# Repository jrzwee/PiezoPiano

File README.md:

# PiezoPiano
PiezoPiano is a PCB piano which can play one octave - all at once. It is programmed via Arduino. It is available for purchase in my [Tindie Store](https://www.tindie.com/products/zaan/piezo-piano/). 

If you like this project, feel free to support me 😇

## Setup for the Arduino IDE
This project is based on the great work of Hans with his [MegaCoreX](https://github.com/MCUdude/MegaCoreX). Visit this repo for further install instructions.
Select following settings in the Arduino IDE:

✅ **Board**: ATmega4809 \
✅ **COM Port**: Select the one your PiezoPiano is connected to \
✅ **Bootloader**: Optiboot (UART1 default pins) \
✅ **Pinout**: 48 pin standard

## Pinout

## Build of Material - BOM
TBD as there is a refactoring in the making.

## Renders

## License
[CERN-OHL-S](https://ohwr.org/cern_ohl_s_v2.pdf)

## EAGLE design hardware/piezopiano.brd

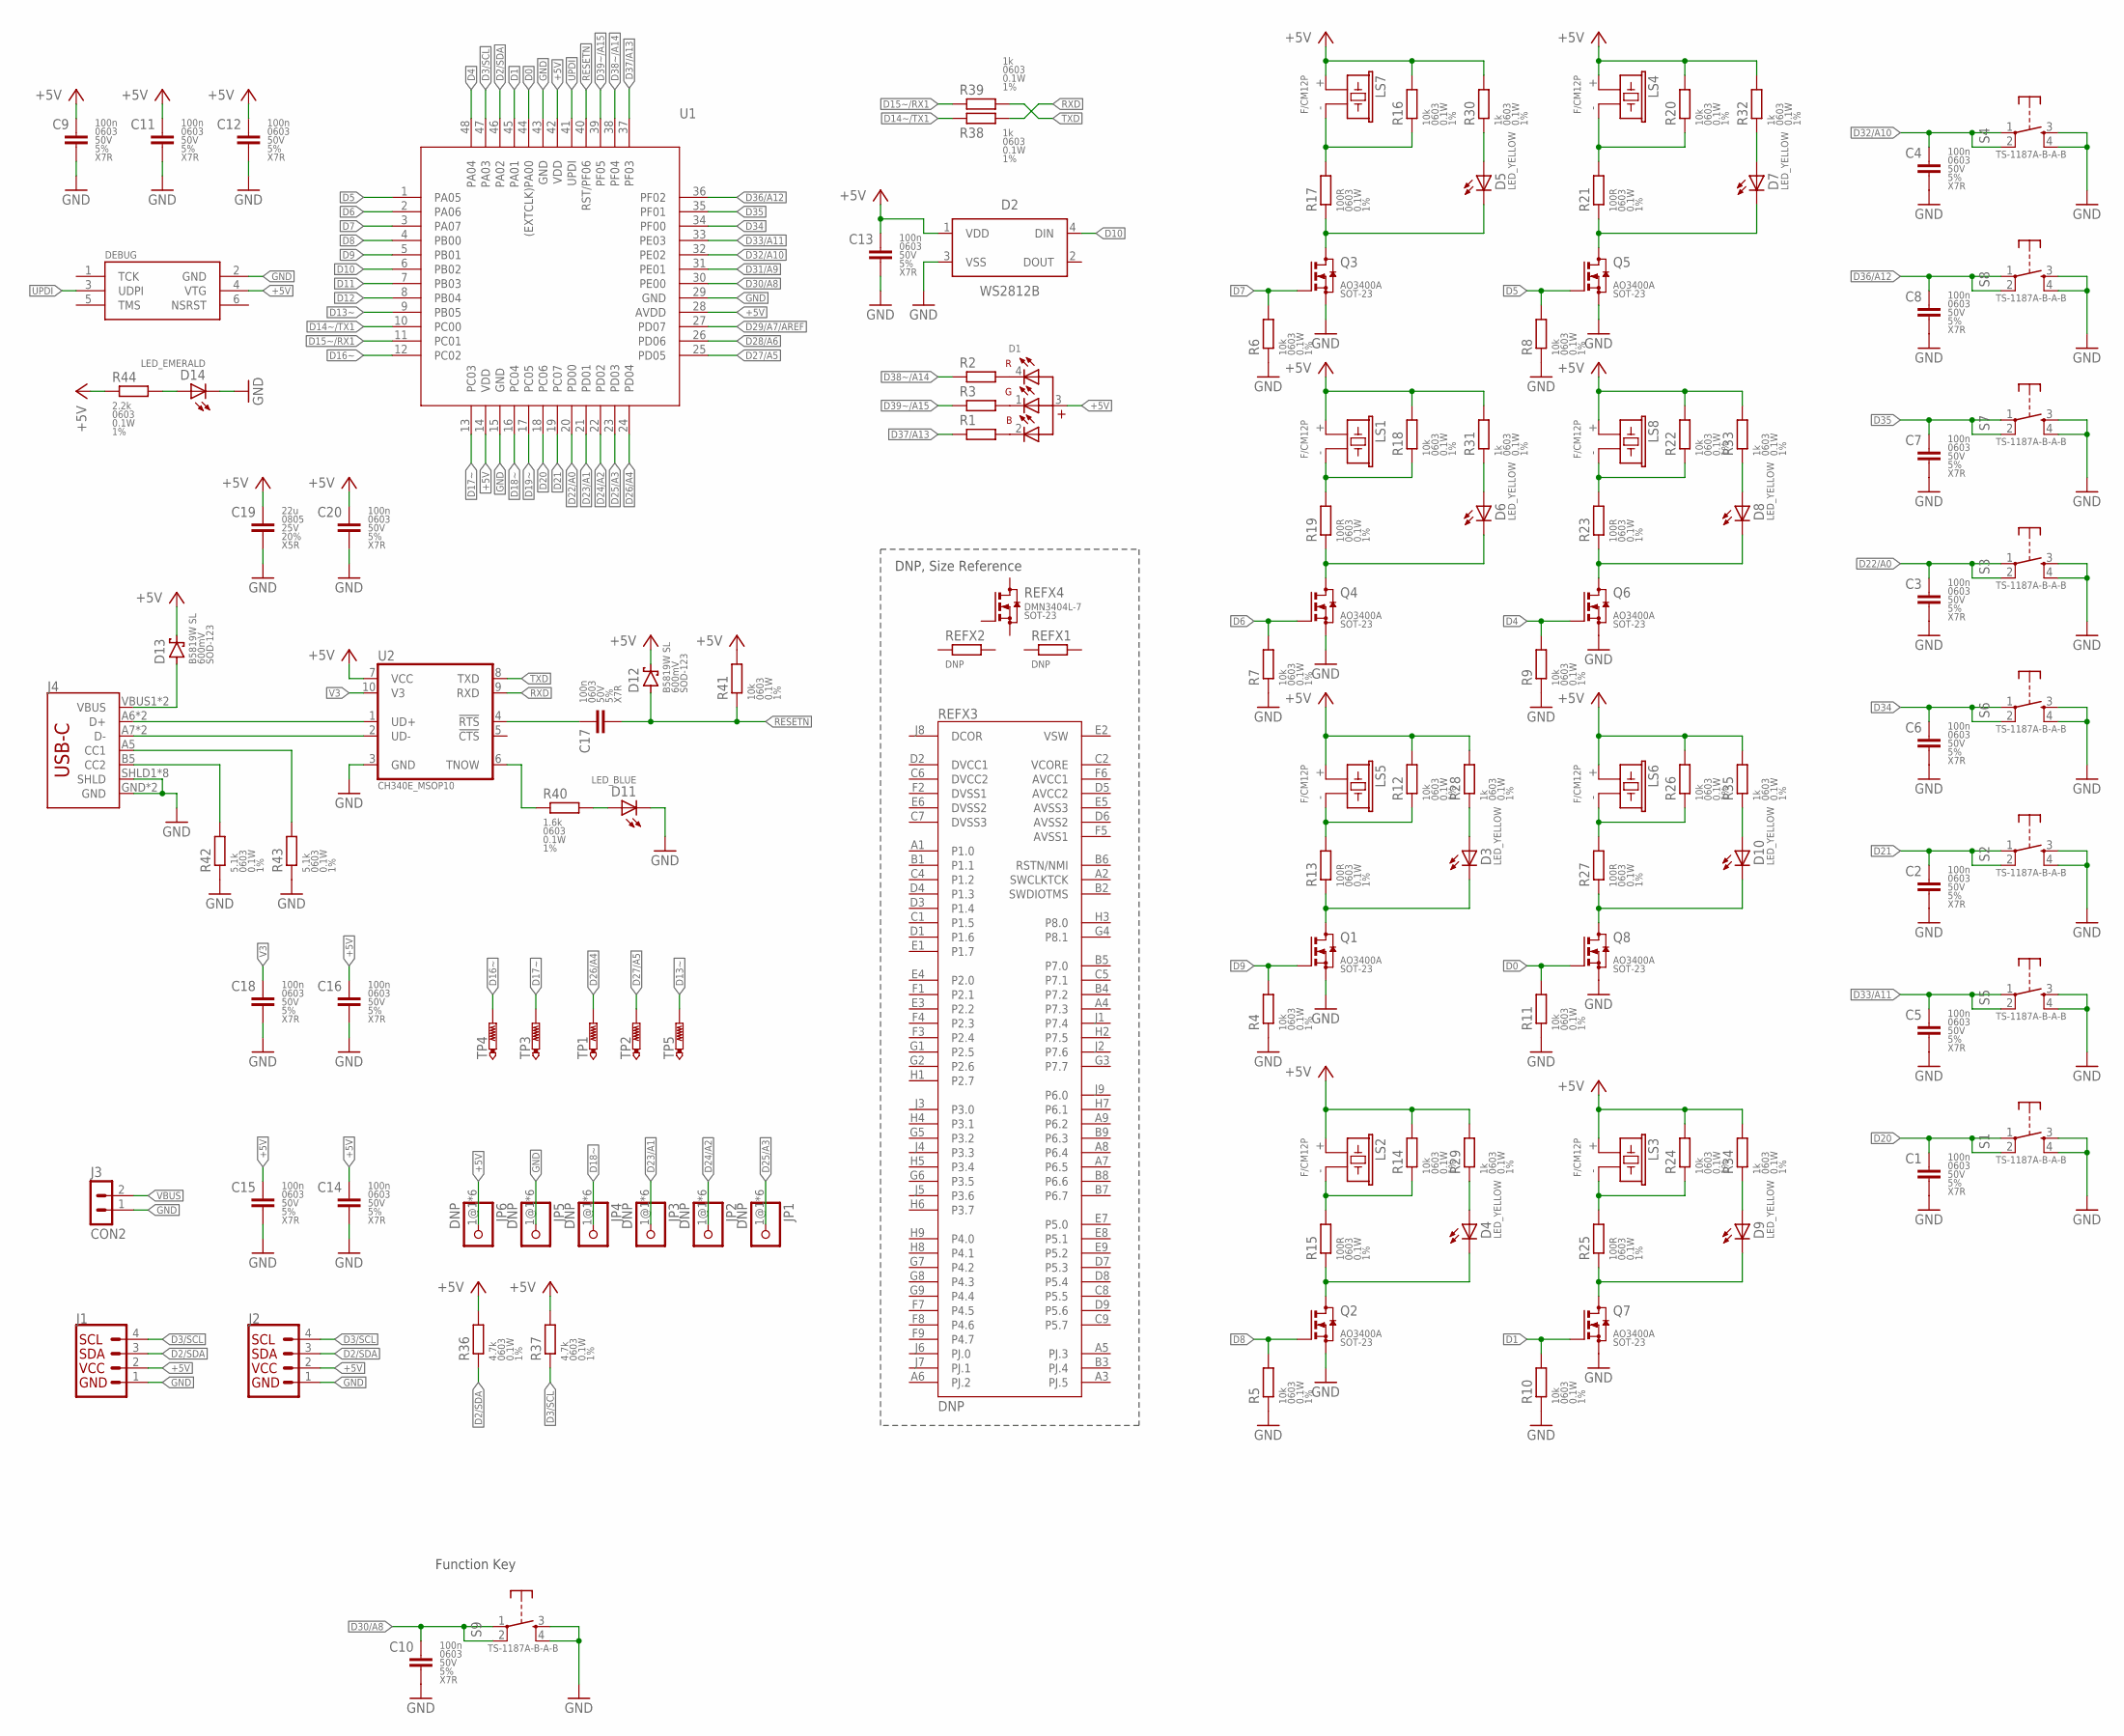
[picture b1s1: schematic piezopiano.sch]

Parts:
C1, C2, C3, C4, C5, C6, C7, C8, C9, C10, C11, C12, C13, C14, C15, C16, C17, C18, C20: 100n; C0603
C19: 22u; C0805
D1: E6C1209RGBC3UDAM173000; WL-SFCX_1210
D2: WS2812B
D3, D4, D5, D6, D7, D8, D9, D10: LED_YELLOW; LEDC1608X55N_FLAT
D11: LED_BLUE; LEDC1608X55N_FLAT
D12, D13: B5819WSL; SOD123
D14: LED_EMERALD; LEDC1608X55N_FLAT
DEBUG: DNP; 490107670612_DEBUGGING
J1, J2: QWIIC_CONNECTORJS-1MM; 1X04_1MM_RA
J3: CON2; H2-2.54
J4: USB_C2-LAYER; USB-C-16P
JP1, JP2, JP3, JP4, JP5, JP6: DNP; 1X01
LS1, LS2, LS3, LS4, LS5, LS6, LS7, LS8: F/CM12P; CM12P/5.0P
Q1, Q2, Q3, Q4, Q5, Q6, Q7, Q8: AO3400A; SOT23
R1, R40: 1.6k; R0603
R2, R28, R29, R30, R31, R32, R33, R34, R35, R38, R39: 1k; R0603
R3, R44: 2.2k; R0603
R4, R5, R6, R7, R8, R9, R10, R11, R12, R14, R16, R18, R20, R22, R24, R26, R41: 10k; R0603
R13, R15, R17, R19, R21, R23, R25, R27: 100R; R0603
R36, R37: 4.7k; R0603
R42, R43: 5.1k; R0603
REFX1: DNP; R0603
REFX2: DNP; R0805
REFX3: DNP; BGA80
REFX4: DNP; SOT23
S1, S2, S3, S4, S5, S6, S7, S8, S9: TS-1187A-B-A-B; TACTILE_SWITCH_SMD_5.2MM
TP1, TP2, TP3, TP4, TP5: PTR1B1,27; B1,27
U1: ATMEGA4809; TQFP48
U2: CH340E_MSOP10; MSOP10

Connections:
+5V: C9.1, C11.1, C12.1, C13.1, C14.1, C15.1, C16.1, C19.1, C20.1, D1.3 (4), D2.1 (VDD), D12.C, D13.C, DEBUG.4 (VTG), J1.2 (VCC), J2.2 (VCC), JP6.1@1, JP6.1@2, JP6.1@3, JP6.1@4, JP6.1@5, JP6.1@6, LS1.+ (1), LS2.+ (1), LS3.+ (1), LS4.+ (1), LS5.+ (1), LS6.+ (1), LS7.+ (1), LS8.+ (1), R12.2, R14.2, R16.2, R18.2, R20.2, R22.2, R24.2, R26.2, R28.2, R29.2, R30.2, R31.2, R32.2, R33.2, R34.2, R35.2, R36.2, R37.2, R41.2, R44.1, U1.14 (VDD), U1.28 (AVDD), U1.42 (VDD), U2.7 (VCC)
AVCC1: REFX3.F6 (AVCC1)
AVCC2: REFX3.D5 (AVCC2)
AVSS1: REFX3.F5 (AVSS1)
AVSS2: REFX3.D6 (AVSS2)
AVSS3: REFX3.E5 (AVSS3)
D0: Q8.1 (G), R11.2, U1.44 ((EXTCLK)PA00)
D1: Q7.1 (G), R10.2, U1.45 (PA01)
D2/SDA: J1.3 (SDA), J2.3 (SDA), R36.1, U1.46 (PA02)
D3/SCL: J1.4 (SCL), J2.4 (SCL), R37.1, U1.47 (PA03)
D4: Q6.1 (G), R9.2, U1.48 (PA04)
D5: Q5.1 (G), R8.2, U1.1 (PA05)
D6: Q4.1 (G), R7.2, U1.2 (PA06)
D7: Q3.1 (G), R6.2, U1.3 (PA07)
D8: Q2.1 (G), R5.2, U1.4 (PB00)
D9: Q1.1 (G), R4.2, U1.5 (PB01)
D10: D2.4 (DIN), U1.6 (PB02)
D11: U1.7 (PB03)
D12: U1.8 (PB04)
D13~: TP5.TP, U1.9 (PB05)
D14~/TX1: R38.1, U1.10 (PC00)
D15~/RX1: R39.1, U1.11 (PC01)
D16~: TP4.TP, U1.12 (PC02)
D17~: TP3.TP, U1.13 (PC03)
D18~: JP4.1@1, JP4.1@2, JP4.1@3, JP4.1@4, JP4.1@5, JP4.1@6, U1.16 (PC04)
D19~: U1.17 (PC05)
D20: C1.1, S1.1, S1.2, U1.18 (PC06)
D21: C2.1, S2.1, S2.2, U1.19 (PC07)
D22/A0: C3.1, S3.1, S3.2, U1.20 (PD00)
D23/A1: JP3.1@1, JP3.1@2, JP3.1@3, JP3.1@4, JP3.1@5, JP3.1@6, U1.21 (PD01)
D24/A2: JP2.1@1, JP2.1@2, JP2.1@3, JP2.1@4, JP2.1@5, JP2.1@6, U1.22 (PD02)
D25/A3: JP1.1@1, JP1.1@2, JP1.1@3, JP1.1@4, JP1.1@5, JP1.1@6, U1.23 (PD03)
D26/A4: TP1.TP, U1.24 (PD04)
D27/A5: TP2.TP, U1.25 (PD05)
D28/A6: U1.26 (PD06)
D29/A7/AREF: U1.27 (PD07)
D30/A8: C10.1, S9.1, S9.2, U1.30 (PE00)
D31/A9: U1.31 (PE01)
D32/A10: C4.1, S4.1, S4.2, U1.32 (PE02)
D33/A11: C5.1, S5.1, S5.2, U1.33 (PE03)
D34: C6.1, S6.1, S6.2, U1.34 (PF00)
D35: C7.1, S7.1, S7.2, U1.35 (PF01)
D36/A12: C8.1, S8.1, S8.2, U1.36 (PF02)
D37/A13: R1.1, U1.37 (PF03)
D38~/A14: R2.1, U1.38 (PF04)
D39~/A15: R3.1, U1.39 (PF05)
DCOR: REFX3.J8 (DCOR)
DVCC1: REFX3.D2 (DVCC1)
DVCC2: REFX3.C6 (DVCC2)
DVSS1: REFX3.F2 (DVSS1)
DVSS2: REFX3.E6 (DVSS2)
DVSS3: REFX3.C7 (DVSS3)
GND: C1.2, C2.2, C3.2, C4.2, C5.2, C6.2, C7.2, C8.2, C9.2, C10.2, C11.2, C12.2, C13.2, C14.2, C15.2, C16.2, C18.2, C19.2, C20.2, D2.3 (VSS), D11.C, D14.C, DEBUG.2 (GND), J1.1 (GND), J2.1 (GND), J3.1, J4.GND, J4.GND2 (GND), J4.SHLD1 (SHLD), J4.SHLD2 (SHLD), J4.SHLD3 (SHLD), J4.SHLD4 (SHLD), J4.SHLD5 (SHLD), J4.SHLD6 (SHLD), J4.SHLD7 (SHLD), J4.SHLD8 (SHLD), JP5.1@1, JP5.1@2, JP5.1@3, JP5.1@4, JP5.1@5, JP5.1@6, Q1.2 (S), Q2.2 (S), Q3.2 (S), Q4.2 (S), Q5.2 (S), Q6.2 (S), Q7.2 (S), Q8.2 (S), R4.1, R5.1, R6.1, R7.1, R8.1, R9.1, R10.1, R11.1, R42.1, R43.1, S1.3 (S), S1.4 (S), S2.3 (S), S2.4 (S), S3.3 (S), S3.4 (S), S4.3 (S), S4.4 (S), S5.3 (S), S5.4 (S), S6.3 (S), S6.4 (S), S7.3 (S), S7.4 (S), S8.3 (S), S8.4 (S), S9.3 (S), S9.4 (S), U1.15 (GND), U1.29 (GND), U1.43 (GND), U2.3 (GND)
unnamed: C17.1, U2.4 (!RTS)
unnamed: D6.C, Q4.3 (D), R19.1
unnamed: D3.C, Q1.3 (D), R13.1
unnamed: LS2.- (2), R14.1, R15.2
unnamed: D7.C, Q5.3 (D), R21.1
unnamed: LS8.- (2), R22.1, R23.2
unnamed: D10.C, Q8.3 (D), R27.1
unnamed: D14.A, R44.2
unnamed: D5.C, Q3.3 (D), R17.1
unnamed: LS1.- (2), R18.1, R19.2
unnamed: LS5.- (2), R12.1, R13.2
unnamed: D4.C, Q2.3 (D), R15.1
unnamed: LS4.- (2), R20.1, R21.2
unnamed: D8.C, Q6.3 (D), R23.1
unnamed: LS6.- (2), R26.1, R27.2
unnamed: LS3.- (2), R24.1, R25.2
unnamed: D9.C, Q7.3 (D), R25.1
unnamed: LS7.- (2), R16.1, R17.2
unnamed: R40.1, U2.6 (TNOW)
unnamed: D11.A, R40.2
unnamed: D1.4 (R), R2.2
unnamed: D5.A, R30.1
unnamed: D7.A, R32.1
unnamed: D8.A, R33.1
unnamed: D6.A, R31.1
unnamed: D10.A, R35.1
unnamed: D3.A, R28.1
unnamed: D1.2 (B), R1.2
unnamed: J4.B5 (CC2), R42.2
unnamed: J4.A5 (CC1), R43.2
unnamed: J4.A6 (D+), J4.B6 (D+), U2.1 (UD+)
unnamed: J4.A7 (D-), J4.B7 (D-), U2.2 (UD-)
unnamed: D4.A, R29.1
unnamed: D9.A, R34.1
unnamed: D1.1 (G), R3.2
RESETN: C17.2, D12.A, R41.1, U1.40 (RST/PF06)
RXD: R38.2, U2.9 (RXD)
TXD: R39.2, U2.8 (TXD)
UPDI: DEBUG.3 (UDPI), U1.41 (UPDI)
V3: C18.1, U2.10 (V3)
VBUS: D13.A, J3.2, J4.VBUS1 (VBUS), J4.VBUS2 (VBUS)
VCORE: REFX3.C2 (VCORE)
VSW: REFX3.E2 (VSW)

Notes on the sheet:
DNP, Size Reference
Function Key

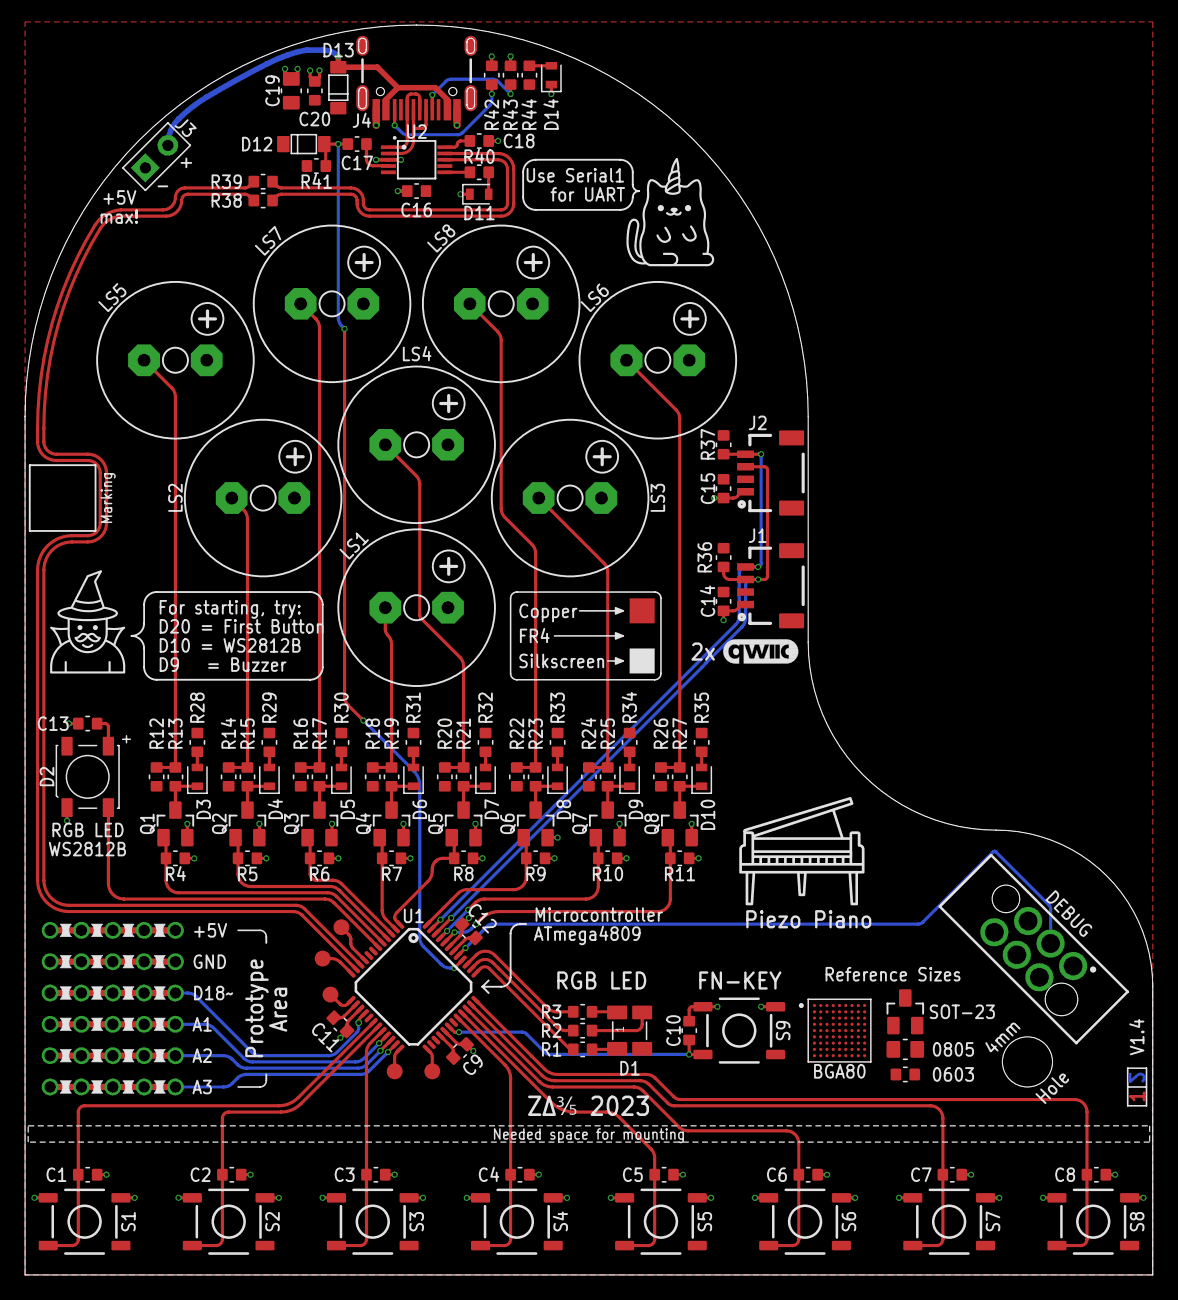
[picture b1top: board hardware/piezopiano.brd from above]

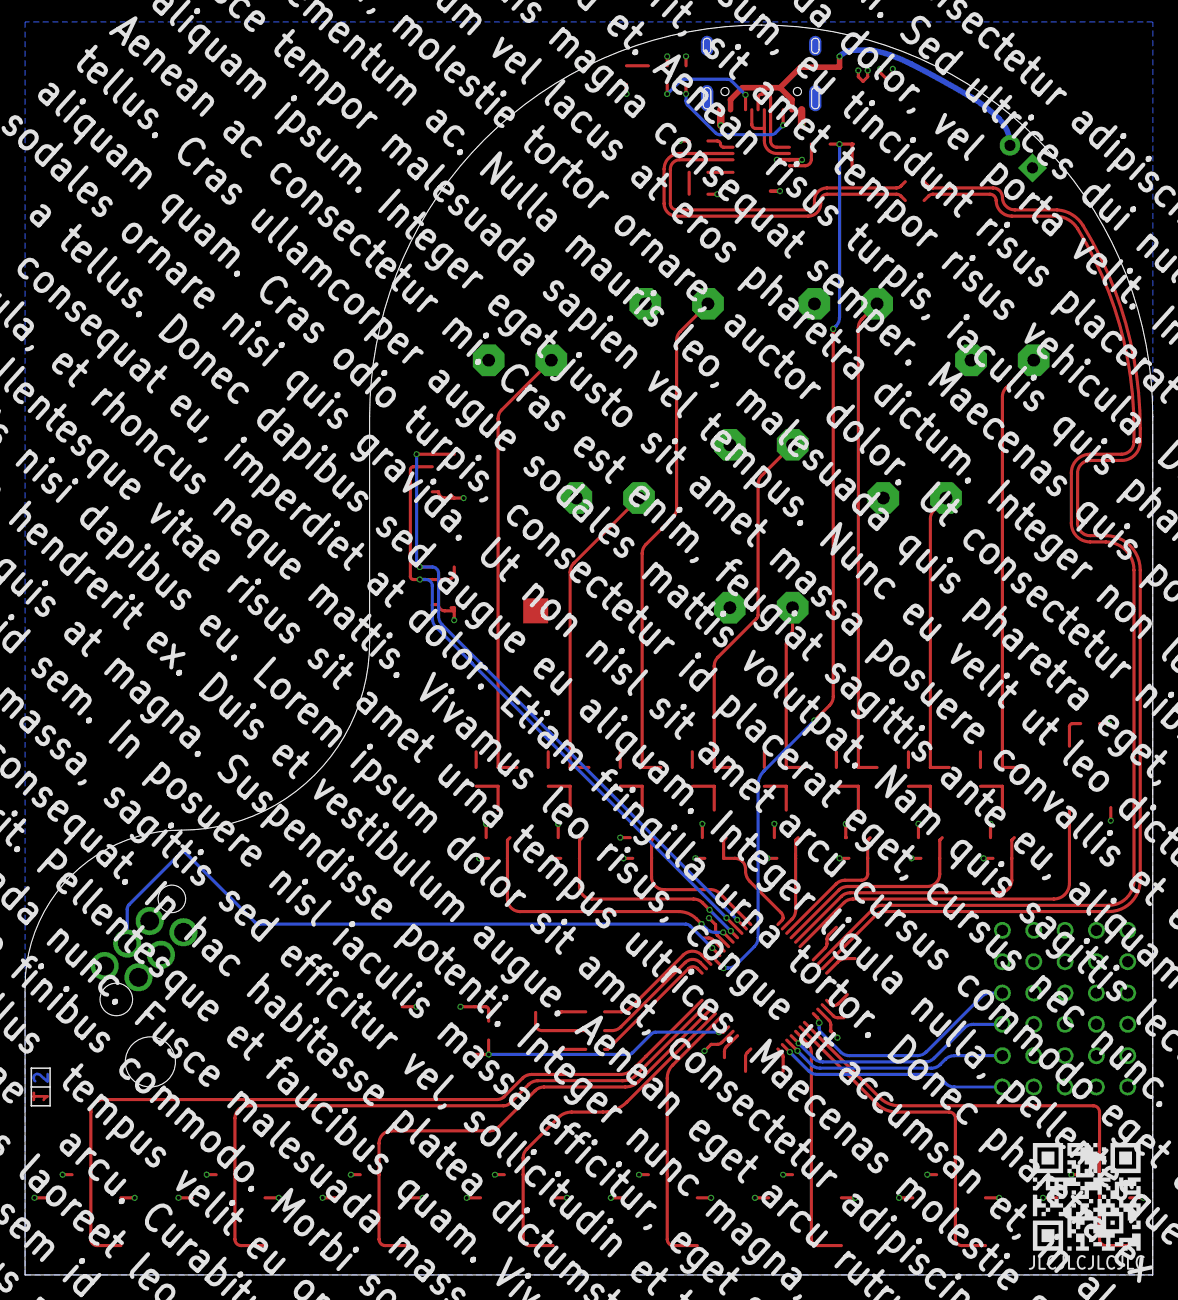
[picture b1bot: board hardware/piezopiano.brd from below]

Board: 2 copper layers, 90.0 x 99.7 mm, 134 parts (2 on the bottom side), 77 nets.

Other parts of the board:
U$1: STACKUP-2L
U$2: PIANO-10MM
U$3: WIZARD-6MM
U$4: QWIIC_6MM
U$5: EXPLANATION-2-2MM
U$6: QR-SPACE
U$7: CATICORN-7MM
U$100: GITHUB-JRZ-10
U$101: JLC_UID

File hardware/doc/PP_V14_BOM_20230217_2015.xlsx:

Model | PP
Version | V1.4
BOM Revision | A
Initials | AZ
Date | 2023-02-17
Description | Qty | Parts | Value | MPN | MF | Info
Chip Capacitor | 19 | C1, C2, C3, C4, C5, C6, C7, C8, C9, C10, C11, C12, C13, C14, C15, C16, C17, C18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 | 100n 0603 50V X7R 5% | CC0603JRX7R9BB104 | Yageo
Chip Resistor | 17 | R4, R5, R6, R7, R8, R9, R10, R11, R12, R14, R16, R18, R20, R22, R24, R26, R41 | 10k 0603 75V 1% | RC0603FR-0710KL | Yageo
Chip Resistor | 11 | R2, R28, R29, R30, R31, R32, R33, R34, R35, R38, R39 | 1k 0603 75V 1% | RC0603FR-071KL | Yageo
Tactile Button SMD | 9 | S1, S2, S3, S4, S5, S6, S7, S8, S9 |  | TS-1187A-B-A-B | XKB Connectivity
Chip Resistor | 8 | R13, R15, R17, R19, R21, R23, R25, R27 | 100R 0603 75V 1% | RC0603FR-07100RL | Yageo
N-CHANNEL MOSFET | 8 | Q1, Q2, Q3, Q4, Q5, Q6, Q7, Q8 | SOT-23 | AO3400A | Alpha & Omega Semicon
Piezo Buzzer | 8 | LS1, LS2, LS3, LS4, LS5, LS6, LS7, LS8 |  | ZL-YDW1207-4005PA-5.0 | ZLFY
CHIP LED FLAT | 8 | D3, D4, D5, D6, D7, D8, D9, D10 | LED_YELLOW | 19-213/Y2C-CQ2R2L/3T(CY) | Everlight Elec
Header SMD 1MM 4Pin | 2 | J1, J2 |  | C145956 | BOOMELE
Chip Resistor | 2 | R1, R40 | 1.6k 0603 75V 1% | RC0603FR-071K6L | Yageo
Chip Resistor | 2 | R36, R37 | 4.7k 0603 75V 1% | RC0603FR-074K7L | Yageo
Chip Resistor | 2 | R42, R43 | 5.1k 0603 75V 1% | RC0603FR-075K1L | Yageo
Schottky Diode | 2 | D12, D13 | SOD-123 | B5819W SL | Changjiang Electronics Tech (CJ)
RGB SMD LED | 1 | D1 | 1210 | E6C1209RGBC3UDA | EKINGLUX
USB Type C Female | 1 | J4 | USB-C 16P | YTC-TC16S-23 | YIYUAN
Chip Resistor | 1 | R3, R44 | 2.2k 0603 75V 1% | RC0603FR-072K2L | Yageo
Chip Capacitor | 1 | C19 | 22u 0805 25V X5R 20% | GRM21BR61E226ME44L | Murata
ATmega4809 Microcontroller | 1 | U1 |  | ATMEGA4809-AFR | Microchip
UART Converter | 1 | U2 | MSOP-10 | CH340E | Jiangsu Qin Heng
CHIP LED FLAT | 1 | D11 | LED_BLUE | 19-217/GHC-YR1S2/3T | Everlight Elec
CHIP LED FLAT | 1 | D14 | LED_EMERALD | 19-217/BHC-ZL1M2RY/3T | Everlight Elec
WS2812 RGB LED | 1 | D2 |  | WS2812B-B/W | WORLDSEMI

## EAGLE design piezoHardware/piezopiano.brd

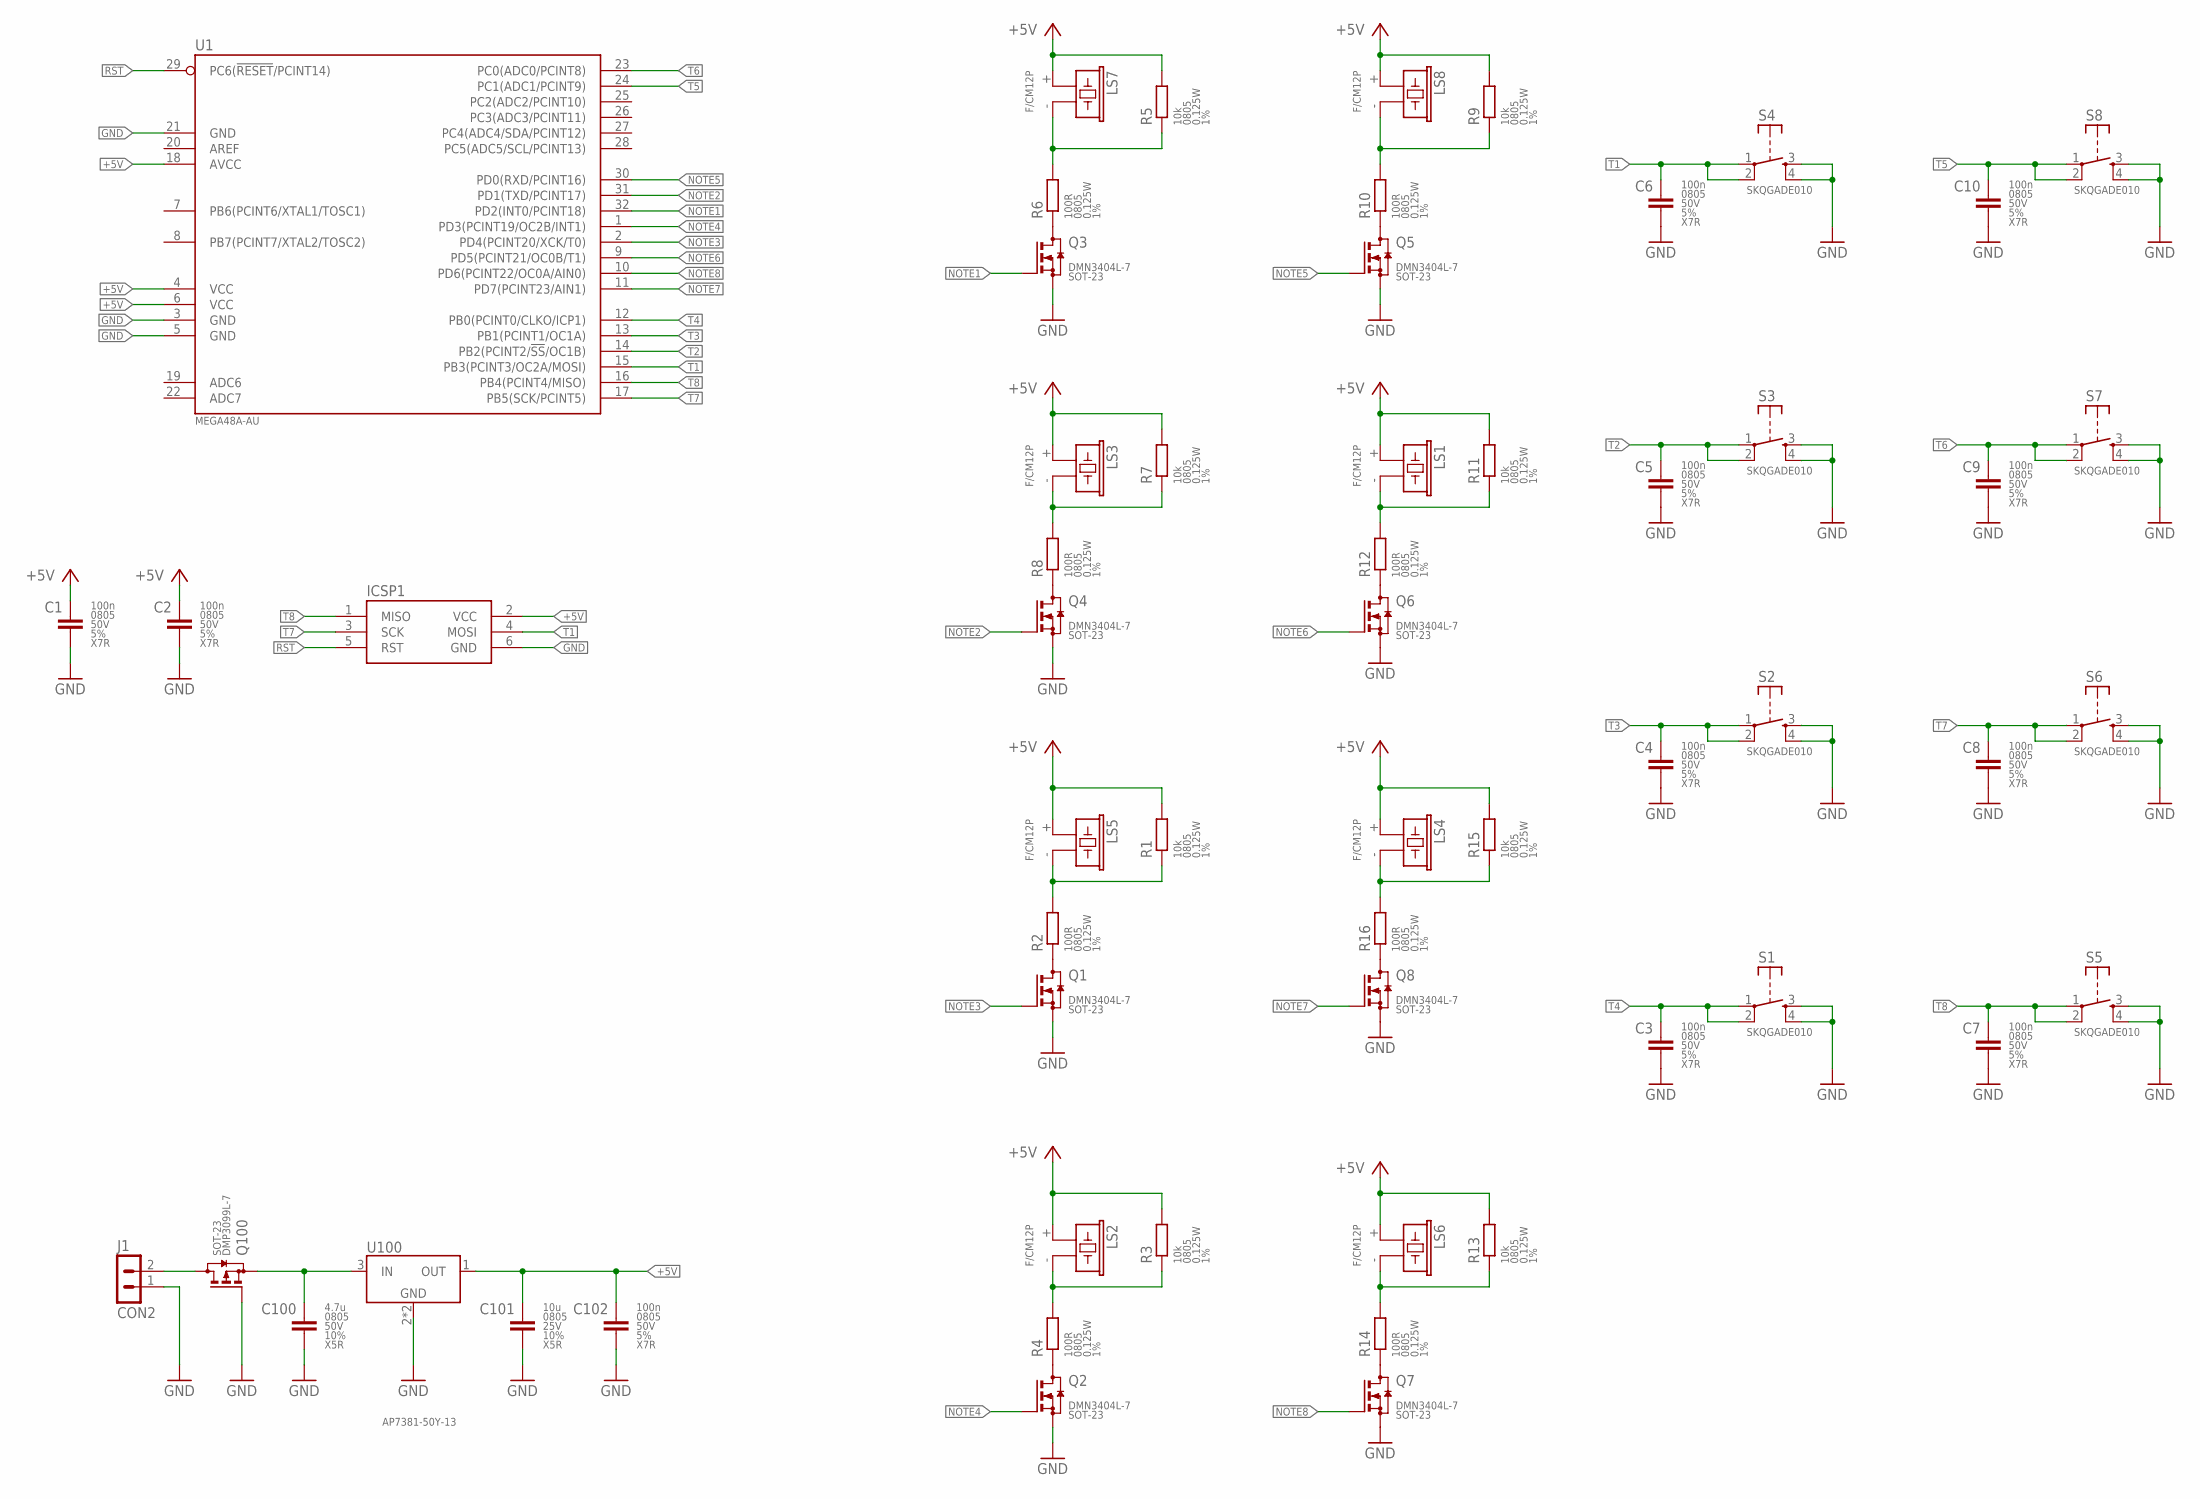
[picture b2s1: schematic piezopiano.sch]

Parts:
C1, C2, C3, C4, C5, C6, C7, C8, C9, C10, C102: 100n; C0805
C100: 4.7u; C0805
C101: 10u; C0805
ICSP1: AVRISP2.54MM; AVRISP-2.54
J1: CON2; H2-2.54
LS1, LS2, LS3, LS4, LS5, LS6, LS7, LS8: F/CM12P; CM12P/5.0P
Q1, Q2, Q3, Q4, Q5, Q6, Q7, Q8: DMN3404L; SOT23
Q100: DMP3099L; SOT23
R1, R3, R5, R7, R9, R11, R13, R15: 10k; R0805
R2, R4, R6, R8, R10, R12, R14, R16: 100R; R0805
S1, S2, S3, S4, S5, S6, S7, S8: SKQGADE010; TACTILE_SWITCH_SMD_5.2MM
U1: MEGA48A-AU; TQFP32-08
U100: AP7381-50Y-13; SOT89

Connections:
+5V: C1.1, C2.1, C101.1, C102.1, ICSP1.2 (VCC), LS1.+ (1), LS2.+ (1), LS3.+ (1), LS4.+ (1), LS5.+ (1), LS6.+ (1), LS7.+ (1), LS8.+ (1), R1.2, R3.2, R5.2, R7.2, R9.2, R11.2, R13.2, R15.2, U1.4 (VCC), U1.6 (VCC), U1.18 (AVCC), U100.1 (OUT)
GND: C1.2, C2.2, C3.2, C4.2, C5.2, C6.2, C7.2, C8.2, C9.2, C10.2, C100.2, C101.2, C102.2, ICSP1.6 (GND), J1.1, Q1.2 (S), Q2.2 (S), Q3.2 (S), Q4.2 (S), Q5.2 (S), Q6.2 (S), Q7.2 (S), Q8.2 (S), Q100.1 (G), S1.3 (S), S1.4 (S), S2.3 (S), S2.4 (S), S3.3 (S), S3.4 (S), S4.3 (S), S4.4 (S), S5.3 (S), S5.4 (S), S6.3 (S), S6.4 (S), S7.3 (S), S7.4 (S), S8.3 (S), S8.4 (S), U1.3 (GND), U1.5 (GND), U1.21 (GND), U100.2 (GND), U100.2@1 (GND)
unnamed: J1.2, Q100.3 (D)
unnamed: Q4.3 (D), R8.1
unnamed: Q1.3 (D), R2.1
unnamed: LS2.- (2), R3.1, R4.2
unnamed: Q5.3 (D), R10.1
unnamed: LS1.- (2), R11.1, R12.2
unnamed: Q8.3 (D), R16.1
unnamed: Q7.3 (D), R14.1
unnamed: Q3.3 (D), R6.1
unnamed: LS3.- (2), R7.1, R8.2
unnamed: LS5.- (2), R1.1, R2.2
unnamed: Q2.3 (D), R4.1
unnamed: LS8.- (2), R9.1, R10.2
unnamed: Q6.3 (D), R12.1
unnamed: LS4.- (2), R15.1, R16.2
unnamed: LS6.- (2), R13.1, R14.2
unnamed: C100.1, Q100.2 (S), U100.3 (IN)
unnamed: LS7.- (2), R5.1, R6.2
NOTE1: Q3.1 (G), U1.32 (PD2(INT0/PCINT18))
NOTE2: Q4.1 (G), U1.31 (PD1(TXD/PCINT17))
NOTE3: Q1.1 (G), U1.2 (PD4(PCINT20/XCK/T0))
NOTE4: Q2.1 (G), U1.1 (PD3(PCINT19/OC2B/INT1))
NOTE5: Q5.1 (G), U1.30 (PD0(RXD/PCINT16))
NOTE6: Q6.1 (G), U1.9 (PD5(PCINT21/OC0B/T1))
NOTE7: Q8.1 (G), U1.11 (PD7(PCINT23/AIN1))
NOTE8: Q7.1 (G), U1.10 (PD6(PCINT22/OC0A/AIN0))
RST: ICSP1.5 (RST), U1.29 (PC6(!RESET!/PCINT14))
T1: C6.1, ICSP1.4 (MOSI), S4.1, S4.2, U1.15 (PB3(PCINT3/OC2A/MOSI))
T2: C5.1, S3.1, S3.2, U1.14 (PB2(PCINT2/!SS!/OC1B))
T3: C4.1, S2.1, S2.2, U1.13 (PB1(PCINT1/OC1A))
T4: C3.1, S1.1, S1.2, U1.12 (PB0(PCINT0/CLKO/ICP1))
T5: C10.1, S8.1, S8.2, U1.24 (PC1(ADC1/PCINT9))
T6: C9.1, S7.1, S7.2, U1.23 (PC0(ADC0/PCINT8))
T7: C8.1, ICSP1.3 (SCK), S6.1, S6.2, U1.17 (PB5(SCK/PCINT5))
T8: C7.1, ICSP1.1 (MISO), S5.1, S5.2, U1.16 (PB4(PCINT4/MISO))

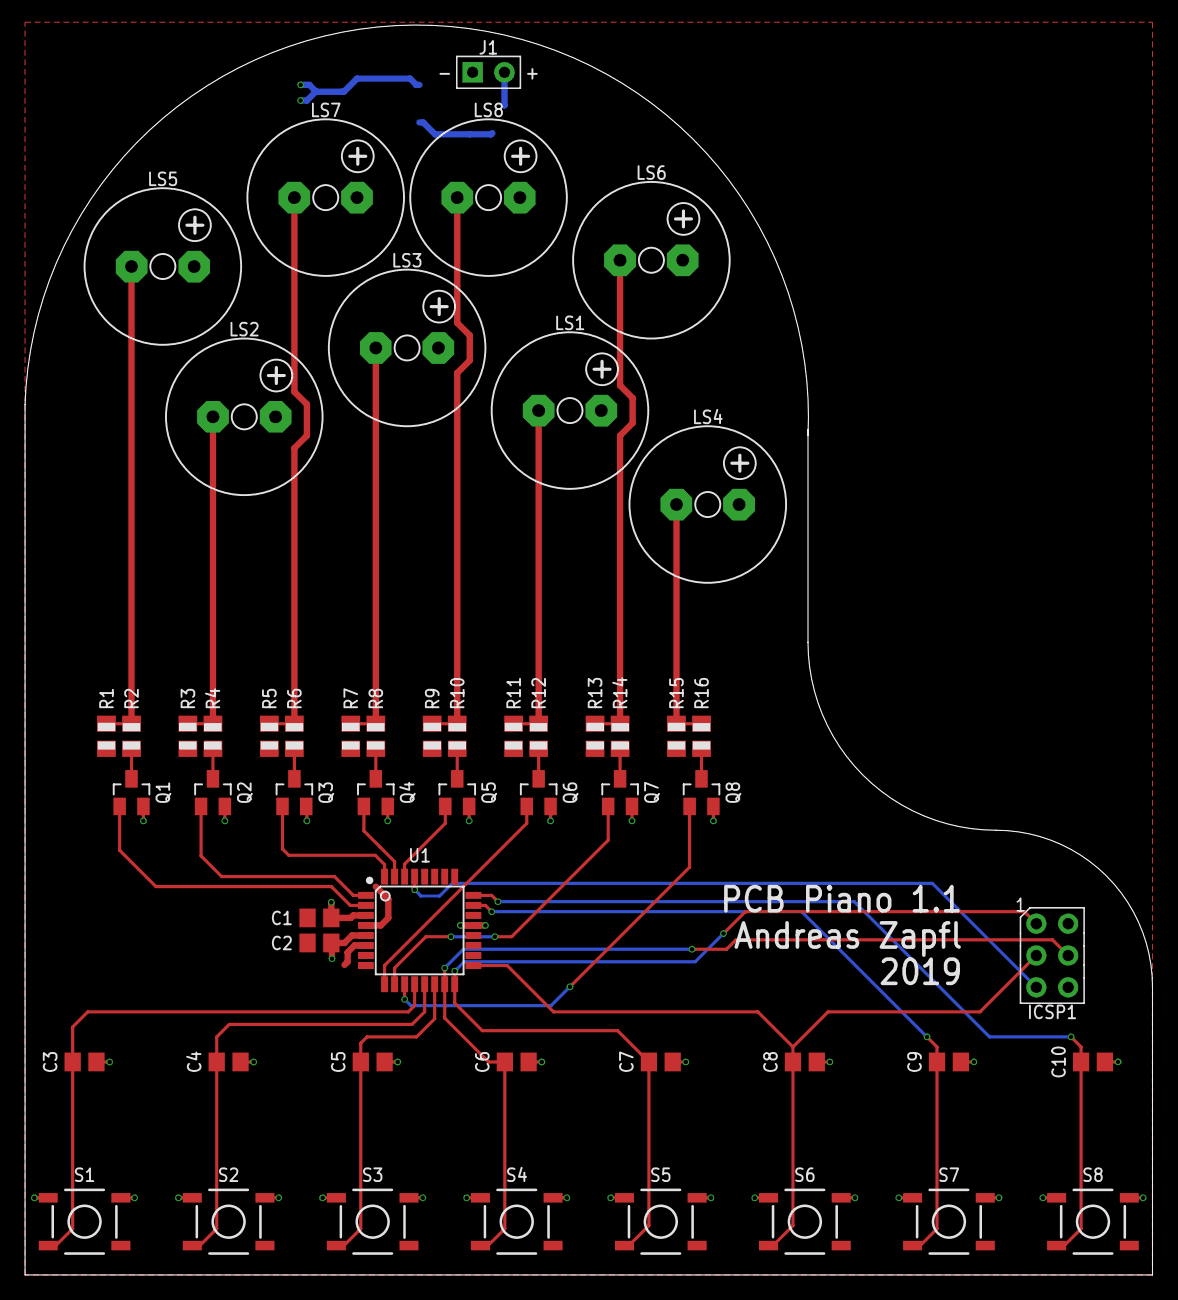
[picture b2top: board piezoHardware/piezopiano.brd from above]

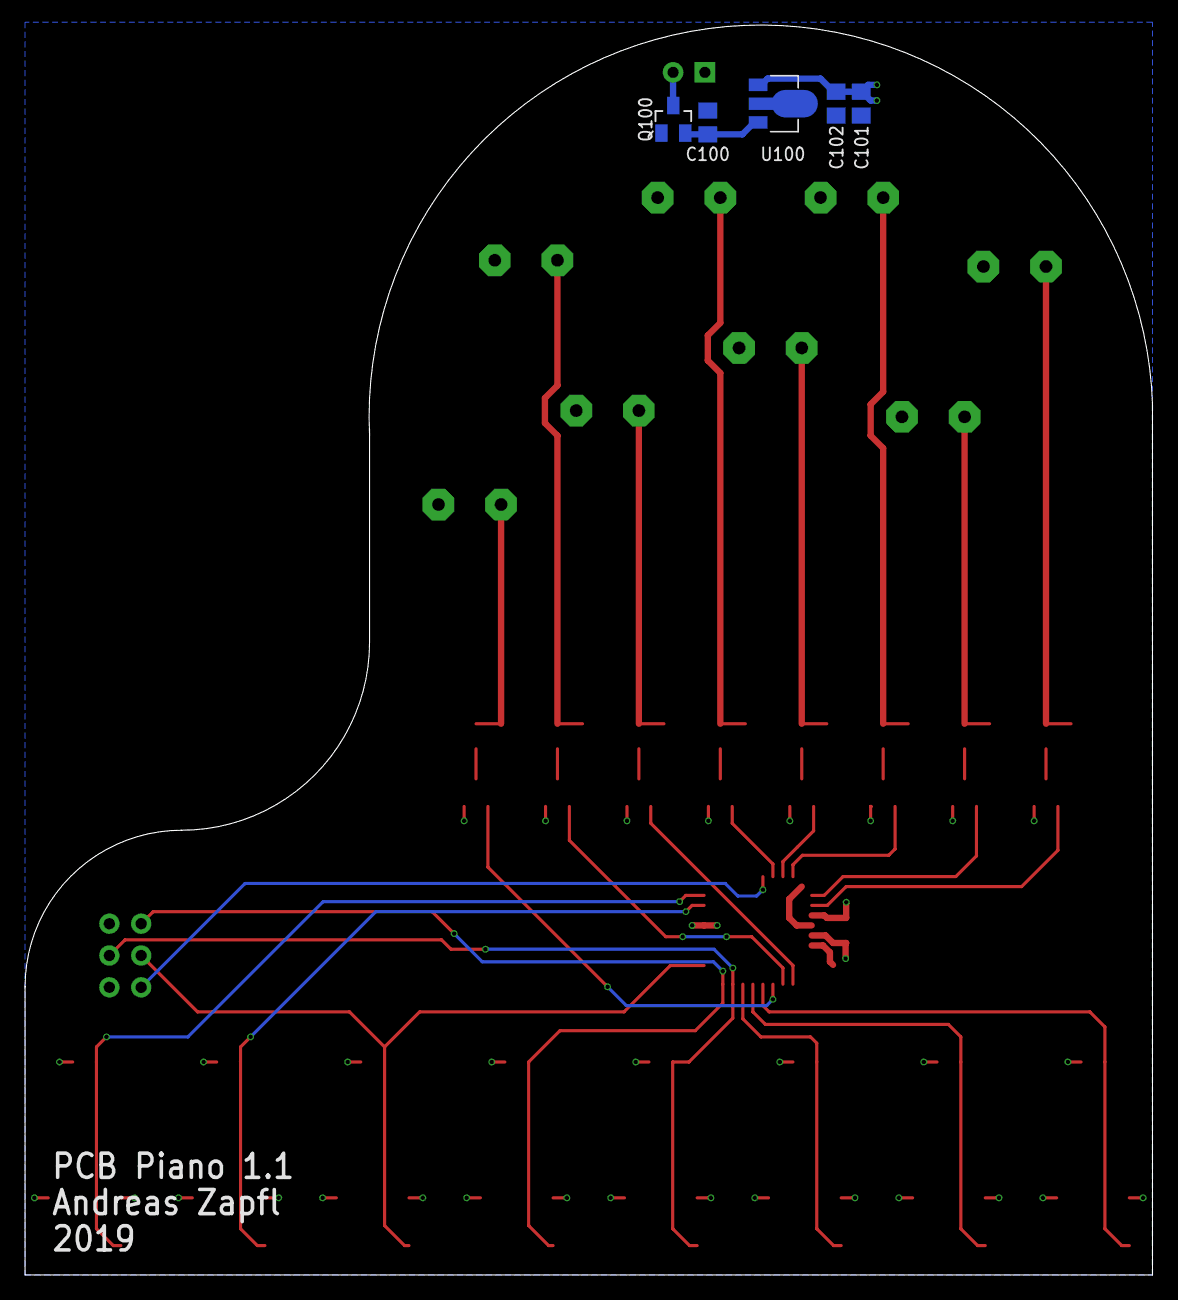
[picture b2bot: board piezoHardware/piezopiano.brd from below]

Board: 2 copper layers, 90.0 x 99.8 mm, 58 parts (5 on the bottom side), 37 nets.

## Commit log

2019-07-11 Initial Commit Working PCB and Code
    Missing downgrade microcontroller and power supply fix
2019-07-11 LDO added
2019-07-15 Frequency correction for note generation
2019-07-15 Minor change unneeded lines
2019-07-15 ATmega silkscreen change
2019-07-16 Partly finished layout
    Missing crystal
2020-01-26 Minor part update
2020-04-23 Restructured folders and added rednders of pcb
2020-04-23 Fitted render for readme
2020-04-23 Added implementation section in readme
2020-07-07 Improved 3D piezo model
2020-08-07 Added USB C and UART
2020-08-07 Added Battery Connector
2020-10-01 Added Battery Management IC
2021-01-24 Update LICENSE
2021-02-07 Changed to 328 for Arduino support
    Changed to ATmega328
    Fixed radius from outline
    Corrected CH340E
    Changed Pinout 328
2021-02-07 Test cutout battery connector
2021-02-07 Added RGB LED
2021-02-10 Added inductor, corrected LED
2021-02-24 Added housing information and shifted piezo to be symmetric
2021-02-24 Mirrored piezos
2021-06-08 Added roundness to footprints
2021-06-08 Changed ICSP
2021-06-08 Changed pin naming at atmega328
2021-09-13 Changed to 4809
2021-09-17 Added proto area
2021-09-20 Placement changes
2021-09-26 Minor routing updates
2021-09-26 Created different branch for battery support, deleted battery parts
2021-09-26 Added QWIIC connector
2021-09-26 Mounting info added
2021-09-26 Deleted not needed wire
2021-09-26 Added round wires
2021-09-27 Routing and Placement changes
2021-09-30 Added PCB artwork
2021-09-30 Added parts for size reference
2021-10-01 Schematic cleanup
2021-10-01 Text for bottom added
2021-10-01 Fixed bottom artwork
2021-10-01 Updated artwork
2021-10-03 Changed artwork to own design
2021-10-03 Updated 3D files
2021-10-03 Added 3D step files for connector
2021-10-03 Rounded traces
2021-10-03 Wizard speaks
2021-10-10 Routing first draft finished
2021-10-10 Added layer explenation
2021-10-10 Changed silkscreen
2021-10-12 Added pictures
2021-10-12 Updated drills
2021-10-15 Renumbered, Gerbers Created
2021-10-20 Added 3d cad files
2021-10-20 Added USB cutout
2021-10-20 Added I2C cutouts
2021-10-23 Added qwiic logo
2021-10-23 Updated silkscreen, created Gerber
2021-10-23 Updated font size in description
2021-10-23 Added images and updated device data
2021-10-23 Changed silk, generated Gerber, updated bom
2021-10-23 Added interactive bom
2021-10-24 Reverted to local libraries
2021-10-24 Cleanup renders
2021-10-24 Added bom infos
2021-10-24 Added csv bom
2021-10-24 updated picture to v1.2
2021-10-24 added mf files
2021-11-12 Fixed silkscreen errors
2021-12-29 Added G-Code
2021-12-29 Updated to 4809
2021-12-29 Added UART RST
2022-01-06 Routed RST
2022-01-06 Added diode, renamed pins to pinout
2022-01-09 Pinout change piezos, silkscreen edit
2022-01-09 Added caps for I2C
2022-01-11 WS2812 pinout bugfix
2022-01-22 Prototype area adapted
2022-01-22 Fixed proto area
2022-01-22 Added 2 TP
2022-01-22 Increased hole size to 4mm
2022-01-25 Added pulldown resistors
2022-01-25 Minor fix, created gerbers and data
2022-02-05 Updated 3D models
2022-02-05 Updated Soldermask Color and added pictures
2022-02-05 Added files for pinout creation
2022-02-28 Fixed 10k resistor
2022-02-28 Fixed WS2812 LED
2022-02-28 Added Arduino Test file
2022-03-02 Added interrupts and WE led to testfirmware
2022-03-03 Interrupt working
2022-03-03 Segmented into different tests
2022-03-03 Updated CAD
2022-03-03 Working Piano
2022-03-03 Splitted timer start stop function
2022-03-03 Restructured variables
2022-03-03 Bugfix size and name
2022-03-03 Pinout added
2022-03-03 Added QWIIC
2022-03-03 Fixed QWIIC print
2022-03-03 Renamed pinout
2022-03-04 Added picture for pixel-measure
2022-03-04 Adde pinout
2022-03-04 Added 512x512 render
2022-03-04 Added 700x700 render
2022-04-06 Fixed LED bug and tuned sound
2022-04-07 Tuned sound by pianist
2022-04-07 Updated tuning for 442 Hz, added LED effect
    Offset 10 creates 448 Hz A4
    Offset 8 creates 442 Hz A4
2022-04-07 Bugfix notes
2022-12-18 Working on new version, added pullups for i2c
2022-12-18 Added fn key
2022-12-18 Added testpoints
2022-12-18 Adapted CAD
2022-12-18 Deleted old json
2022-12-18 Silkscreen change
2022-12-18 Changed ws2812 silkscreen, routed power in
2022-12-18 Added correct revision number
2022-12-18 Renumber
2022-12-19 Rework folder structure
2022-12-28 Added LCSC MPNs
2022-12-28 Changed RGB MPN
2023-01-10 Created MF files
2023-01-11 Updated LCSC parts
2023-02-17 CAD rework
2023-02-17 Minor fixes and data generation
2023-02-17 Updated bom
2023-03-10 Clean Up Schematic
